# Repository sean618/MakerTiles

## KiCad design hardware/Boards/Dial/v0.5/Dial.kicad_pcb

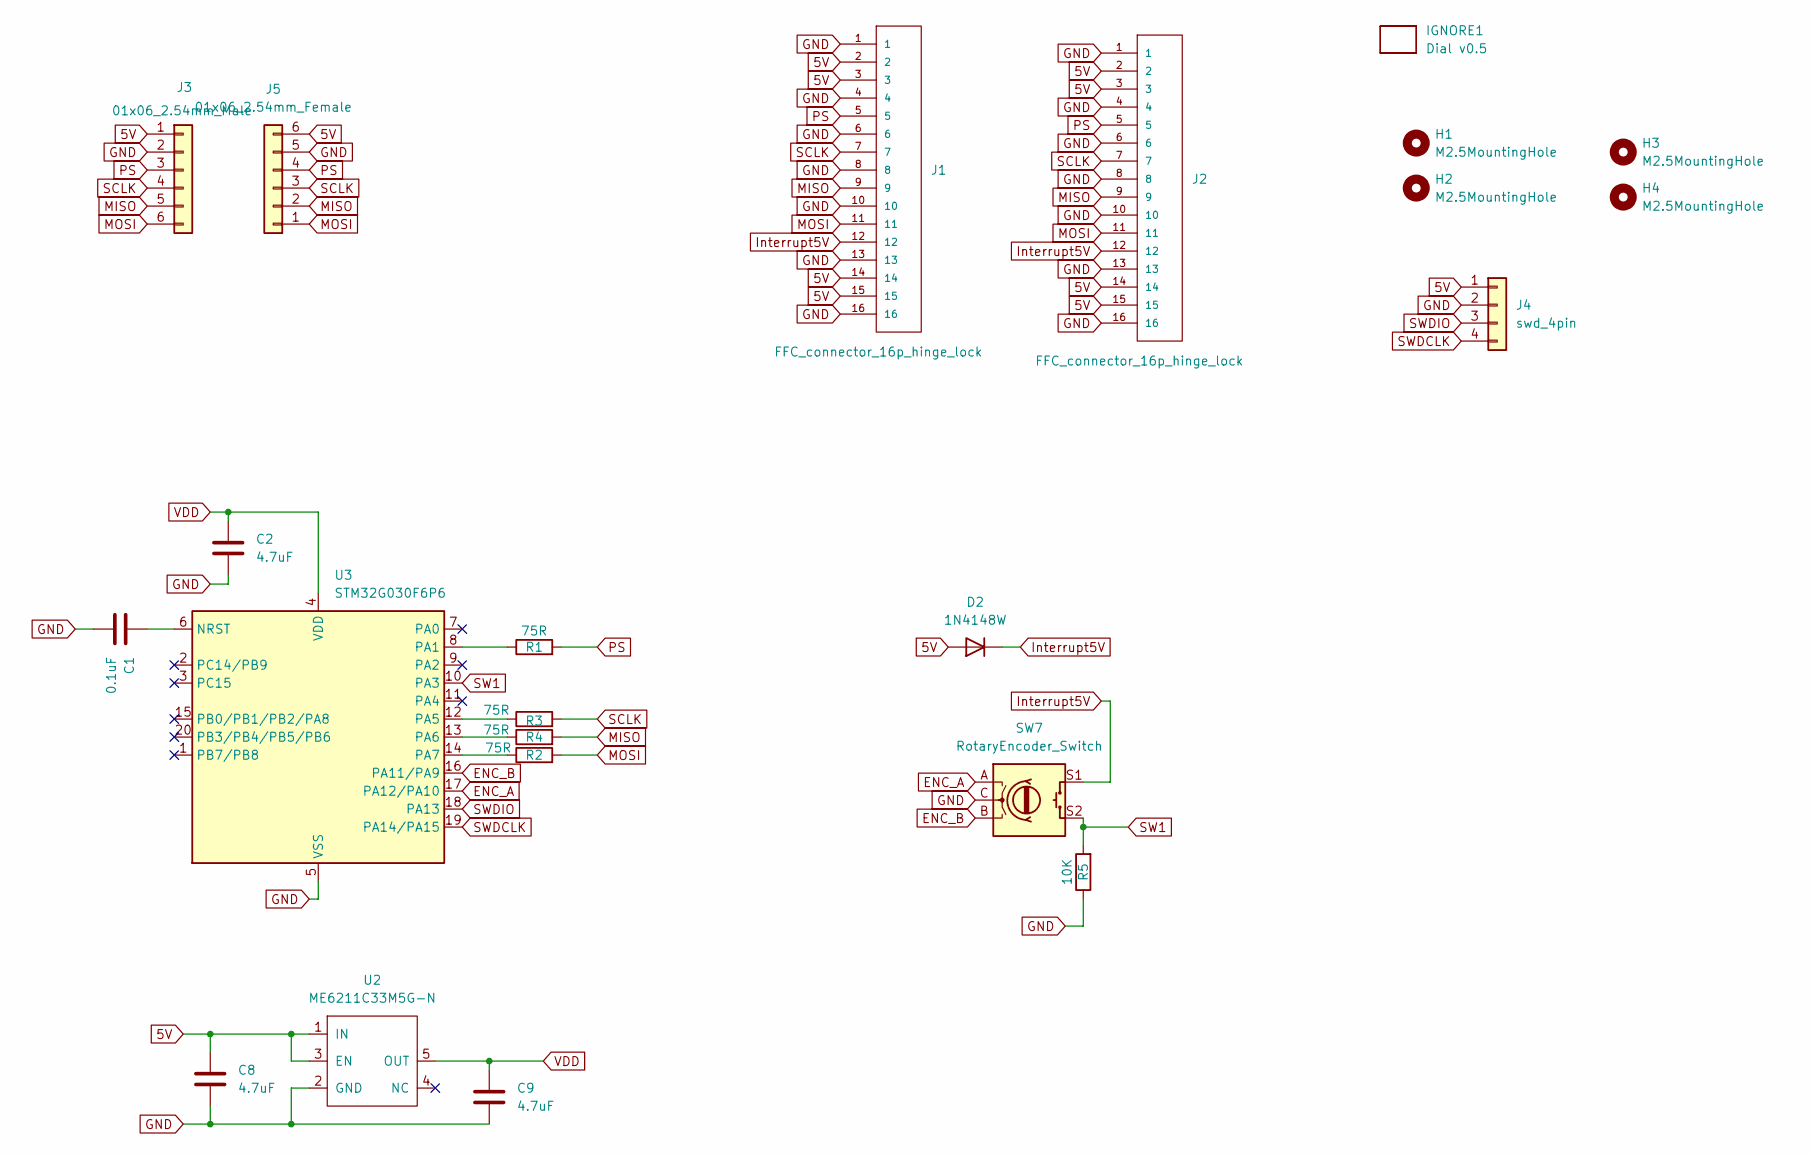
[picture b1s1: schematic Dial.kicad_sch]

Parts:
C1: 0.1uF; C_0402_1005Metric
C2, C8, C9: 4.7uF; C_0402_1005Metric
D2: 1N4148W; D_SOD-123
H1, H2, H3, H4: M2.5MountingHole; MountingHole_2.7mm_M2.5_ISO7380
IGNORE1: Dial v0.5; BoardText
J1, J2: FFC_connector_16p_hinge_lock
J3: 01x06_2.54mm_Male
J4: swd_4pin; swd_header
J5: 01x06_2.54mm_Female
R1, R2, R3, R4: 75R; R_0402_1005Metric
R5: 10K; R_0402_1005Metric
SW7: RotaryEncoder_Switch; RotaryEncoderEC12D
U2: ME6211C33M5G-N; SOT-23-5
U3: STM32G030F6P6; TSSOP-20_4.4x6.5mm_P0.65mm

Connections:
5V: C8.1, D2.2 (A), J1.2, J1.3, J1.14, J1.15, J2.2, J2.3, J2.14, J2.15, J3.1, J4.1, J5.6, U2.1 (IN), U2.3 (EN)
ENC_A: SW7.A, U3.17 (PA12/PA10)
ENC_B: SW7.B, U3.16 (PA11/PA9)
GND: C1.2, C2.2, C8.2, C9.2, J1.1, J1.4, J1.6, J1.8, J1.10, J1.13, J1.16, J2.1, J2.4, J2.6, J2.8, J2.10, J2.13, J2.16, J3.2, J4.2, J5.5, R5.1, SW7.C, U2.2 (GND), U3.5 (VSS)
Interrupt5V: D2.1 (K), J1.12, J2.12, SW7.S1
MISO: J1.9, J2.9, J3.5, J5.2, R4.2
MOSI: J1.11, J2.11, J3.6, J5.1, R2.2
unnamed: C1.1, U3.6 (NRST)
unnamed: R1.1, U3.8 (PA1)
unnamed: R3.1, U3.12 (PA5)
unnamed: R4.1, U3.13 (PA6)
unnamed: R2.1, U3.14 (PA7)
PS: J1.5, J2.5, J3.3, J5.4, R1.2
SCLK: J1.7, J2.7, J3.4, J5.3, R3.2
SW1: R5.2, SW7.S2, U3.10 (PA3)
SWDCLK: J4.4, U3.19 (PA14/PA15)
SWDIO: J4.3, U3.18 (PA13)
VDD: C2.1, C9.1, U2.5 (OUT), U3.4 (VDD)

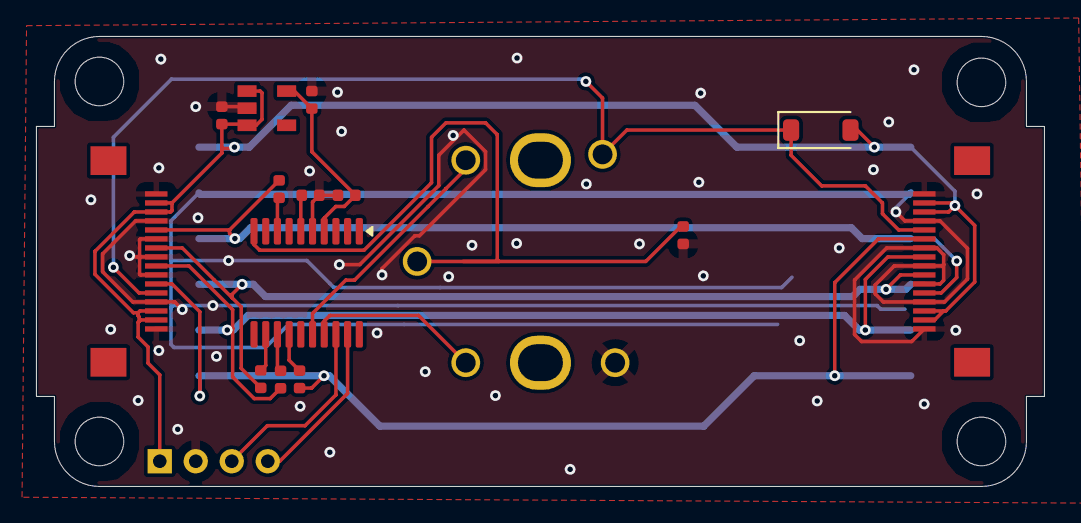
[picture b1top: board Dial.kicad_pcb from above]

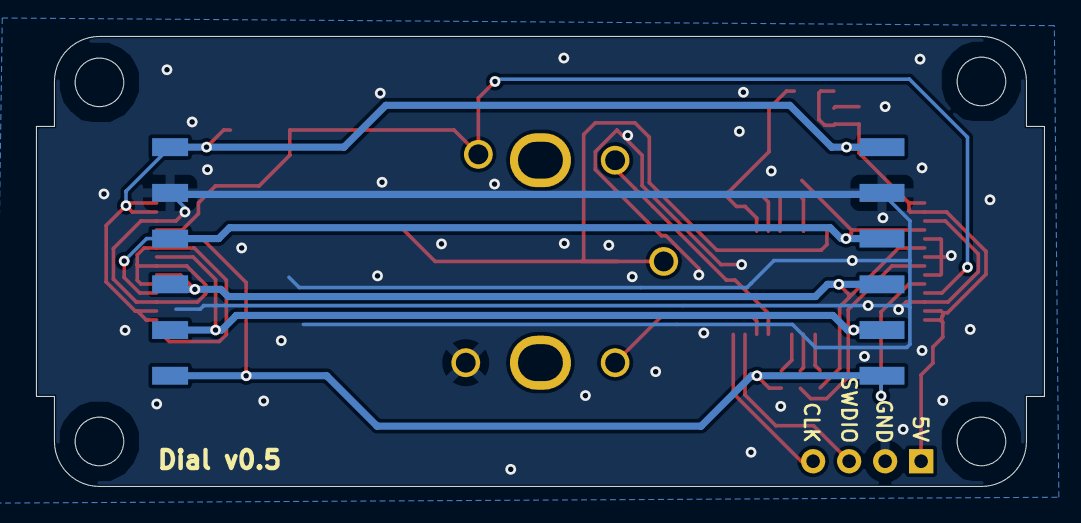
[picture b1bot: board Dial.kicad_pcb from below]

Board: 2 copper layers, 56.0 x 25.0 mm, 23 parts (2 on the bottom side), 18 nets.

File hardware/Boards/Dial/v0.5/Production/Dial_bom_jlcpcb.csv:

Comment,Designator,Footprint,LCSC Part Number
4.7uF,"C9,C8,C2",C_0402_1005Metric,C23733
FFC_connector_16p_hinge_lock,"J1,J2",FFC_connector_16p_hinge_lock,C262665
1N4148W,D2,D_SOD-123,C81598
ME6211C33M5G-N,U2,SOT-23-5,C81233
75R,"R2,R4,R1,R3",R_0402_1005Metric,C25133
RotaryEncoder_Switch,SW7,RotaryEncoderEC12D,C112349
STM32G030F6P6,U3,TSSOP-20_4.4x6.5mm_P0.65mm,C529330
10K,R5,R_0402_1005Metric,C25744
0.1uF,C1,C_0402_1005Metric,C1525
01x06_2.54mm_Female,J5,01x06_2.54mm_Female,C5142239
01x06_2.54mm_Male,J3,01x06_2.54mm_Male,C5242199

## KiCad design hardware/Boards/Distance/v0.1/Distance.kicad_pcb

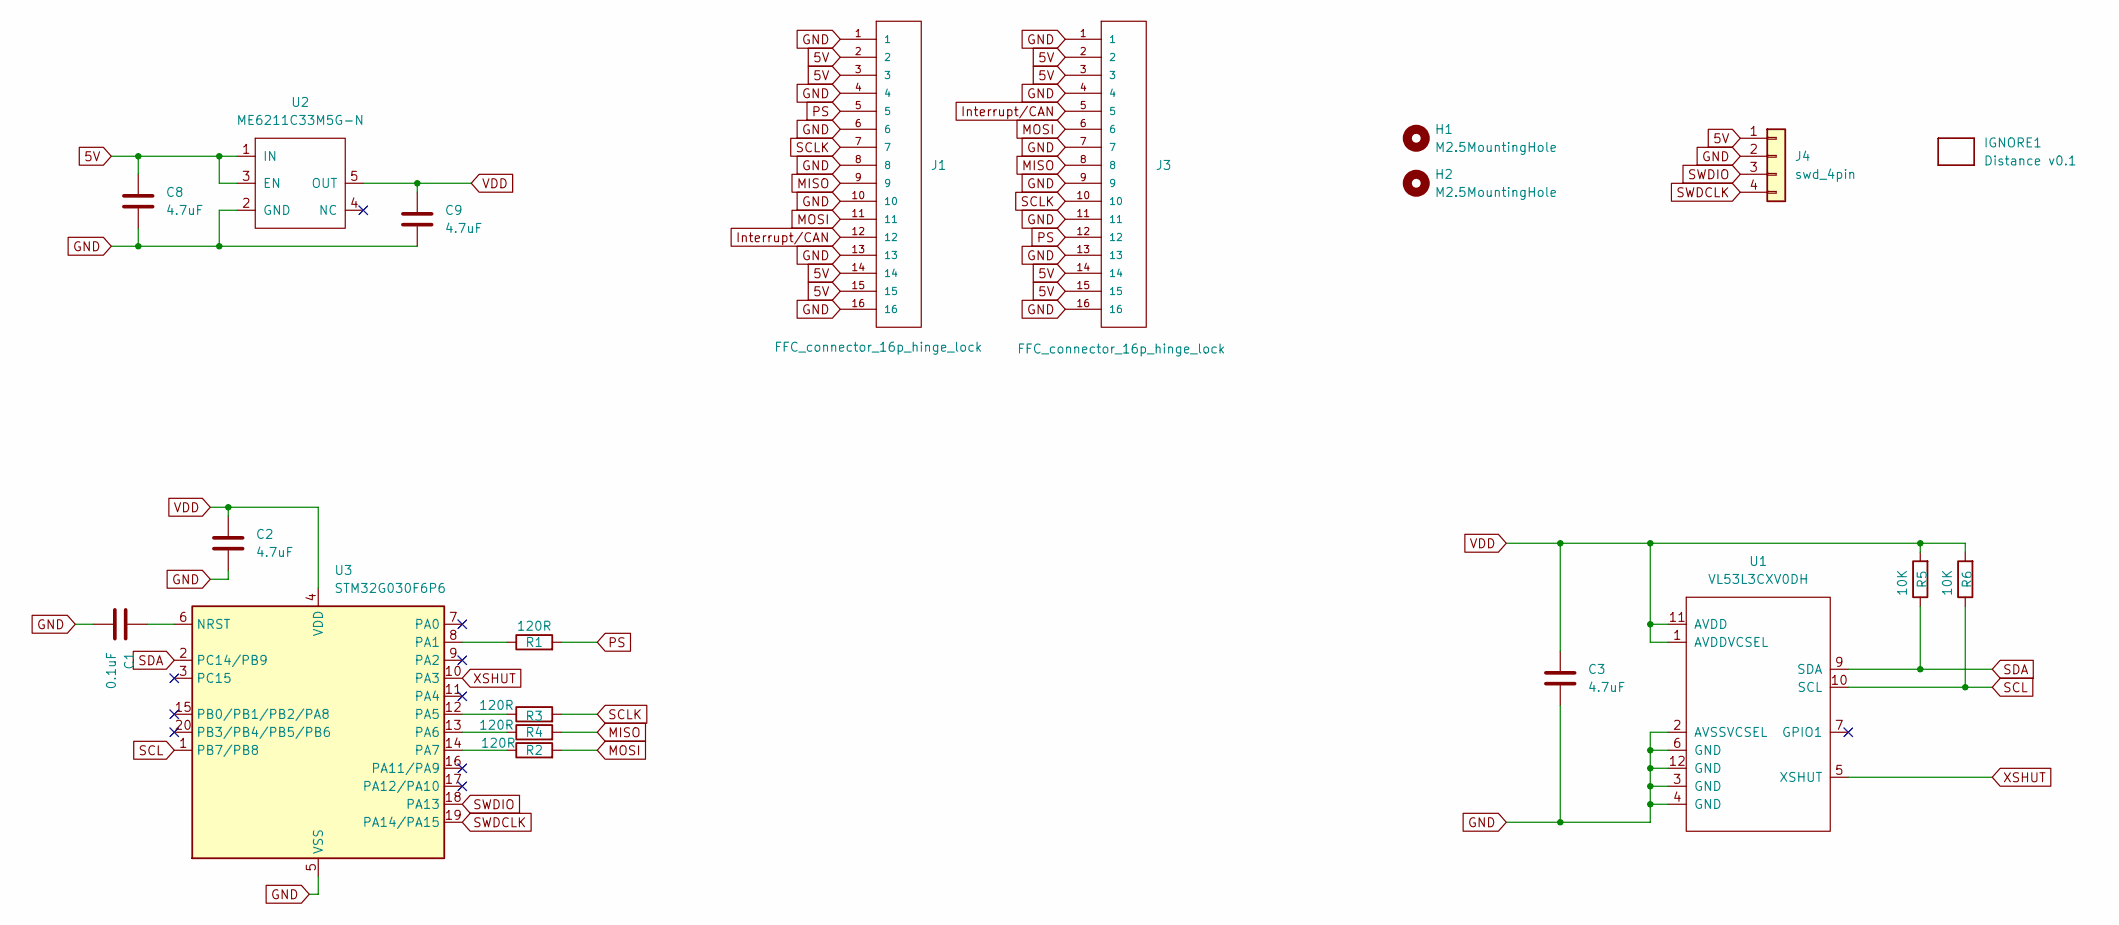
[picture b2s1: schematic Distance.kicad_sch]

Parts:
C1: 0.1uF; C_0402_1005Metric
C2, C3, C8, C9: 4.7uF; C_0402_1005Metric
H1, H2: M2.5MountingHole; MountingHole_2.7mm_M2.5_ISO7380
IGNORE1: Distance v0.1; BoardText
J1, J3: FFC_connector_16p_hinge_lock
J4: swd_4pin; swd_header
R1, R2, R3, R4: 120R; R_0402_1005Metric
R5, R6: 10K; R_0402_1005Metric
U1: VL53L3CXV0DH
U2: ME6211C33M5G-N; SOT-23-5
U3: STM32G030F6P6; TSSOP-20_4.4x6.5mm_P0.65mm

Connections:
5V: C8.1, J1.2, J1.3, J1.14, J1.15, J3.2, J3.3, J3.14, J3.15, J4.1, U2.1 (IN), U2.3 (EN)
GND: C1.2, C2.2, C3.2, C8.2, C9.2, J1.1, J1.4, J1.6, J1.8, J1.10, J1.13, J1.16, J3.1, J3.4, J3.7, J3.9, J3.11, J3.13, J3.16, J4.2, U1.2 (AVSSVCSEL), U1.3 (GND), U1.4 (GND), U1.6 (GND), U1.12 (GND), U2.2 (GND), U3.5 (VSS)
Interrupt/CAN: J1.12, J3.5
MISO: J1.9, J3.8, R4.2
MOSI: J1.11, J3.6, R2.2
unnamed: C1.1, U3.6 (NRST)
unnamed: R1.1, U3.8 (PA1)
unnamed: R3.1, U3.12 (PA5)
unnamed: R4.1, U3.13 (PA6)
unnamed: R2.1, U3.14 (PA7)
PS: J1.5, J3.12, R1.2
SCL: R6.1, U1.10 (SCL), U3.1 (PB7/PB8)
SCLK: J1.7, J3.10, R3.2
SDA: R5.1, U1.9 (SDA), U3.2 (PC14/PB9)
SWDCLK: J4.4, U3.19 (PA14/PA15)
SWDIO: J4.3, U3.18 (PA13)
VDD: C2.1, C3.1, C9.1, R5.2, R6.2, U1.1 (AVDDVCSEL), U1.11 (AVDD), U2.5 (OUT), U3.4 (VDD)
XSHUT: U1.5 (XSHUT), U3.10 (PA3)

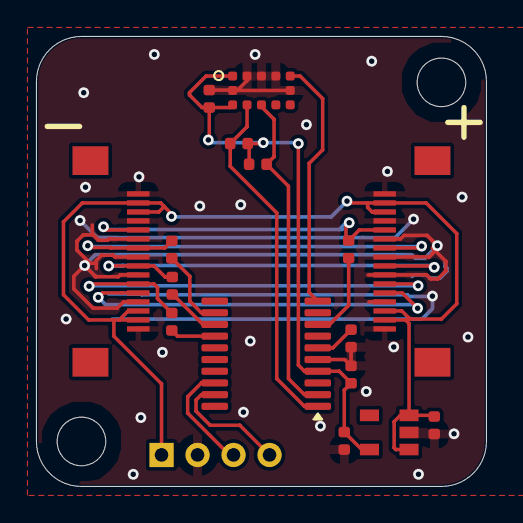
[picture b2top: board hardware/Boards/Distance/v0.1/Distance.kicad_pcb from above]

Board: 4 copper layers, 25.0 x 25.0 mm, 20 parts (0 on the bottom side), 18 nets.

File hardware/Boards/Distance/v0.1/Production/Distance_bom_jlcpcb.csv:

Comment,Designator,Footprint,LCSC Part Number
4.7uF,"C9,C8,C2,C3",C_0402_1005Metric,C23733
FFC_connector_16p_hinge_lock,"J1,J3",FFC_connector_16p_hinge_lock,C262665
10K,"R5,R6",R_0402_1005Metric,C25744
ME6211C33M5G-N,U2,SOT-23-5,C81233
VL53L3CXV0DH,U1,VL53L3CXV0DH,C1864163
120R,"R2,R3,R4,R1",R_0402_1005Metric,C25079
STM32G030F6P6,U3,TSSOP-20_4.4x6.5mm_P0.65mm,C529330
0.1uF,C1,C_0402_1005Metric,C1525

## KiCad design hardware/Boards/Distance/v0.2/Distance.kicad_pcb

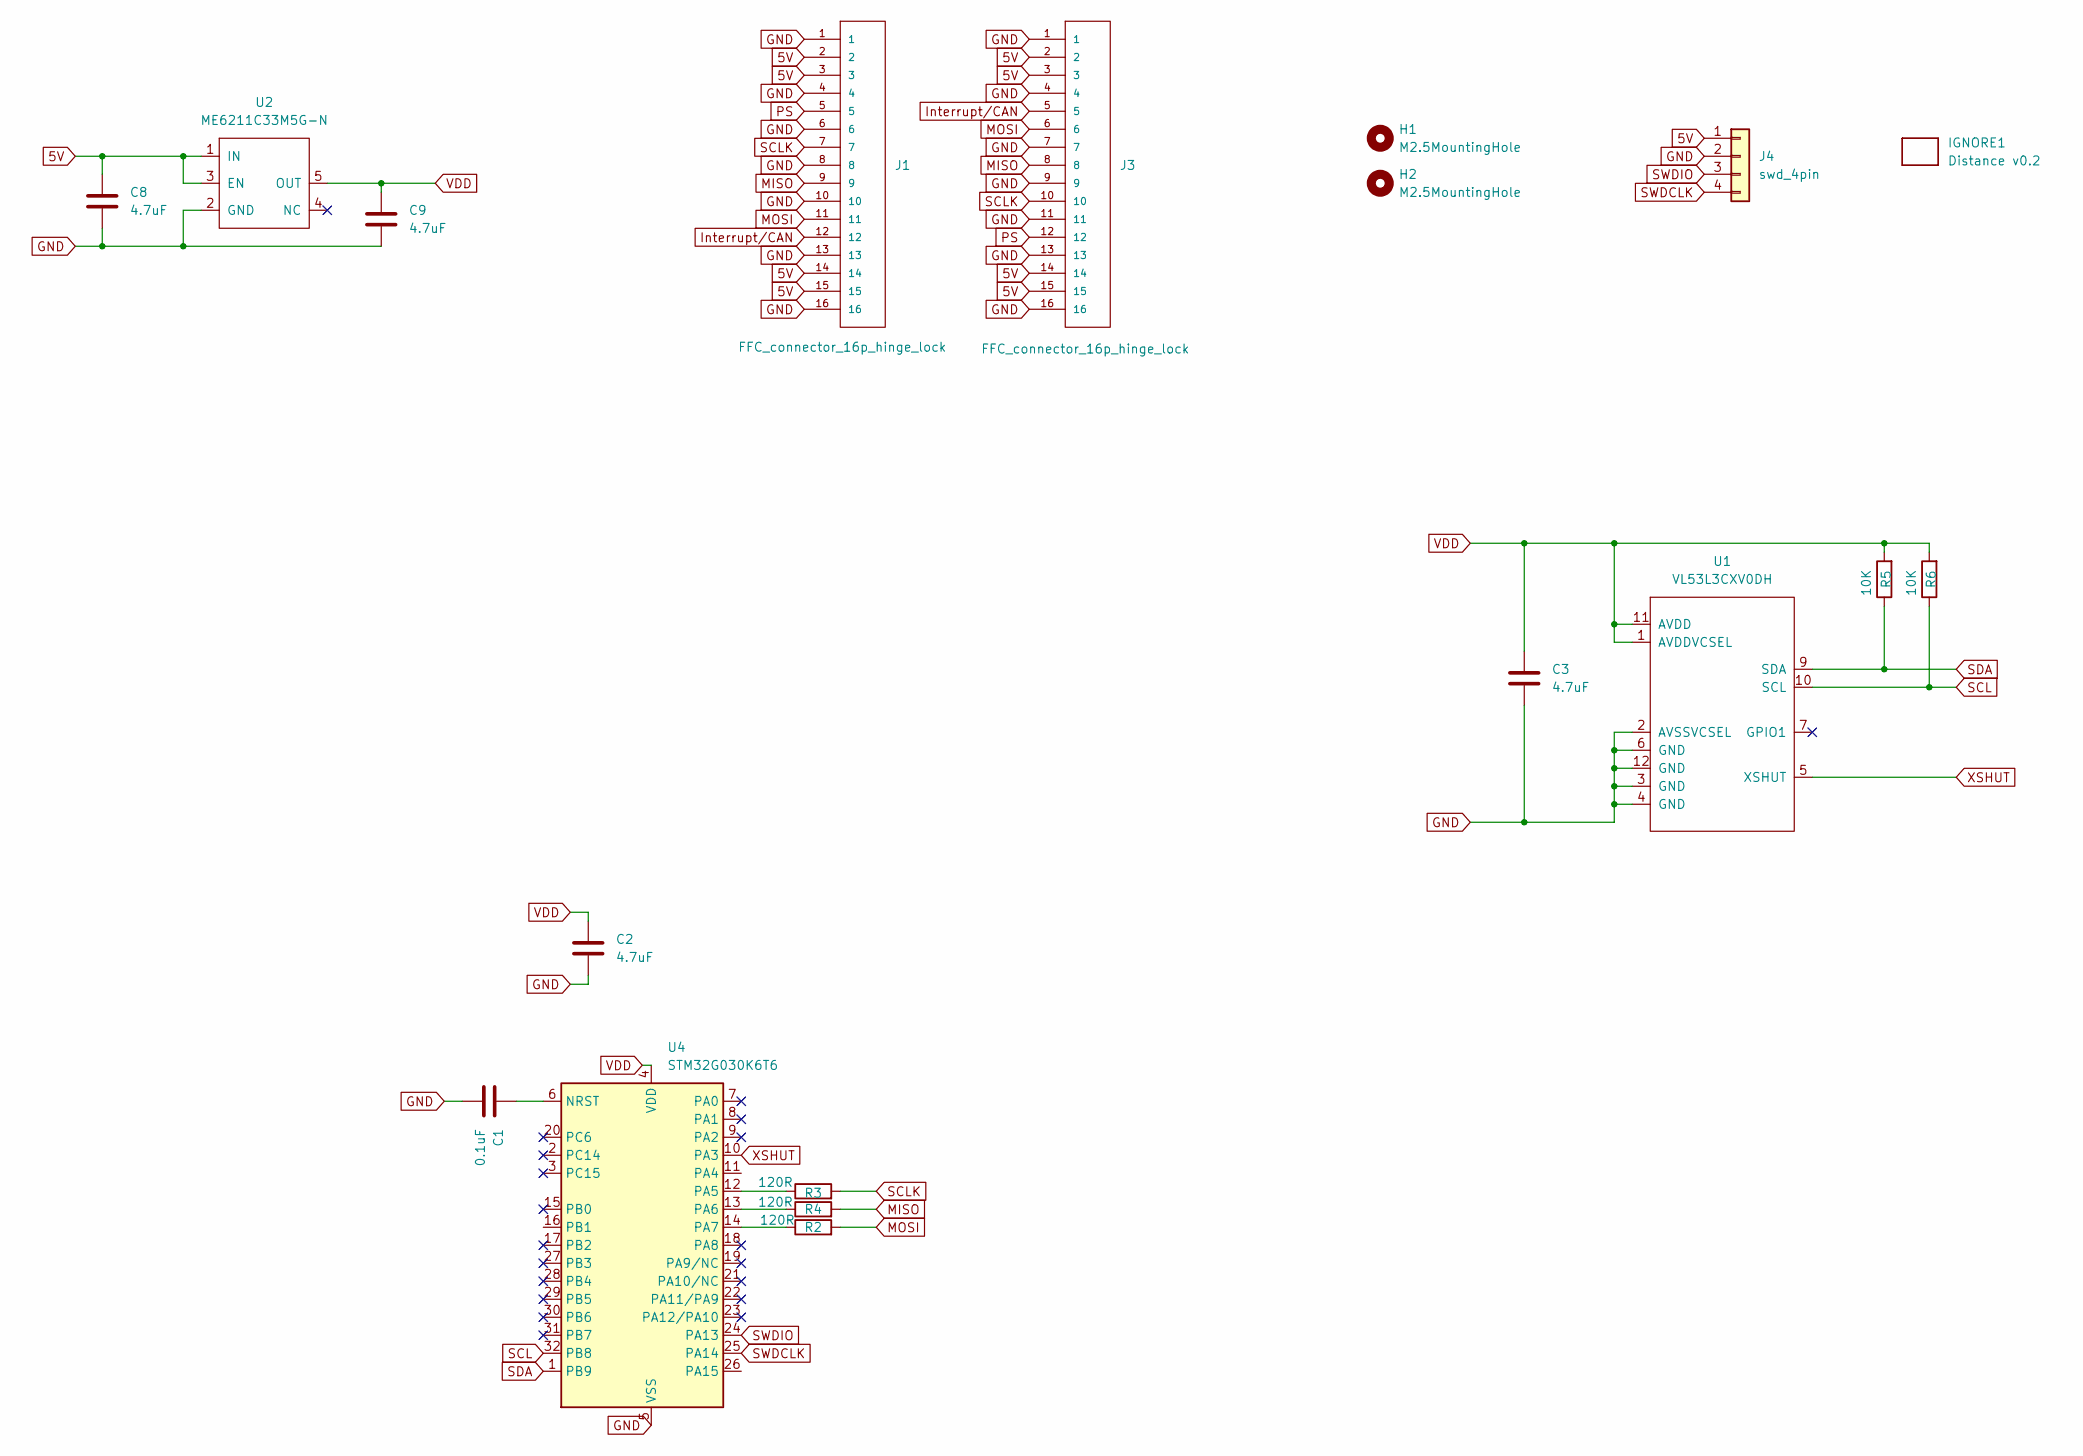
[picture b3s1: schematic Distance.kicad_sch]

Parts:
C1: 0.1uF; C_0402_1005Metric
C2, C3, C8, C9: 4.7uF; C_0402_1005Metric
H1, H2: M2.5MountingHole; MountingHole_2.7mm_M2.5_ISO7380
IGNORE1: Distance v0.2; BoardText
J1, J3: FFC_connector_16p_hinge_lock
J4: swd_4pin; swd_header
R2, R3, R4: 120R; R_0402_1005Metric
R5, R6: 10K; R_0402_1005Metric
U1: VL53L3CXV0DH
U2: ME6211C33M5G-N; SOT-23-5
U4: STM32G030K6T6; LQFP-32_7x7mm_P0.8mm

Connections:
5V: C8.1, J1.2, J1.3, J1.14, J1.15, J3.2, J3.3, J3.14, J3.15, J4.1, U2.1 (IN), U2.3 (EN)
GND: C1.2, C2.2, C3.2, C8.2, C9.2, J1.1, J1.4, J1.6, J1.8, J1.10, J1.13, J1.16, J3.1, J3.4, J3.7, J3.9, J3.11, J3.13, J3.16, J4.2, U1.2 (AVSSVCSEL), U1.3 (GND), U1.4 (GND), U1.6 (GND), U1.12 (GND), U2.2 (GND), U4.5 (VSS)
Interrupt/CAN: J1.12, J3.5
MISO: J1.9, J3.8, R4.2
MOSI: J1.11, J3.6, R2.2
unnamed: C1.1, U4.6 (NRST)
unnamed: R3.1, U4.12 (PA5)
unnamed: R4.1, U4.13 (PA6)
unnamed: R2.1, U4.14 (PA7)
PS: J1.5, J3.12
SCL: R6.1, U1.10 (SCL), U4.32 (PB8)
SCLK: J1.7, J3.10, R3.2
SDA: R5.1, U1.9 (SDA), U4.1 (PB9)
SWDCLK: J4.4, U4.25 (PA14)
SWDIO: J4.3, U4.24 (PA13)
VDD: C2.1, C3.1, C9.1, R5.2, R6.2, U1.1 (AVDDVCSEL), U1.11 (AVDD), U2.5 (OUT), U4.4 (VDD)
XSHUT: U1.5 (XSHUT), U4.10 (PA3)

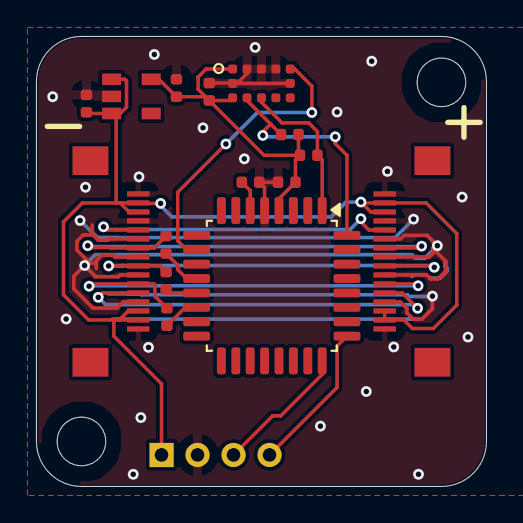
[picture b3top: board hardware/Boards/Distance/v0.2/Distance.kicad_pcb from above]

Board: 4 copper layers, 25.0 x 25.0 mm, 19 parts (0 on the bottom side), 17 nets.

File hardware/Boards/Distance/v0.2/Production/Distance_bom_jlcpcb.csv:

Comment,Designator,Footprint,LCSC Part Number
4.7uF,"C9,C8,C2,C3",C_0402_1005Metric,C23733
FFC_connector_16p_hinge_lock,"J1,J3",FFC_connector_16p_hinge_lock,C262665
10K,"R5,R6",R_0402_1005Metric,C25744
ME6211C33M5G-N,U2,SOT-23-5,C81233
VL53L3CXV0DH,U1,VL53L3CXV0DH,C1864163
120R,"R2,R3,R4",R_0402_1005Metric,C25079
0.1uF,C1,C_0402_1005Metric,C1525
STM32G030K6T6,U4,LQFP-32_7x7mm_P0.8mm,C529331

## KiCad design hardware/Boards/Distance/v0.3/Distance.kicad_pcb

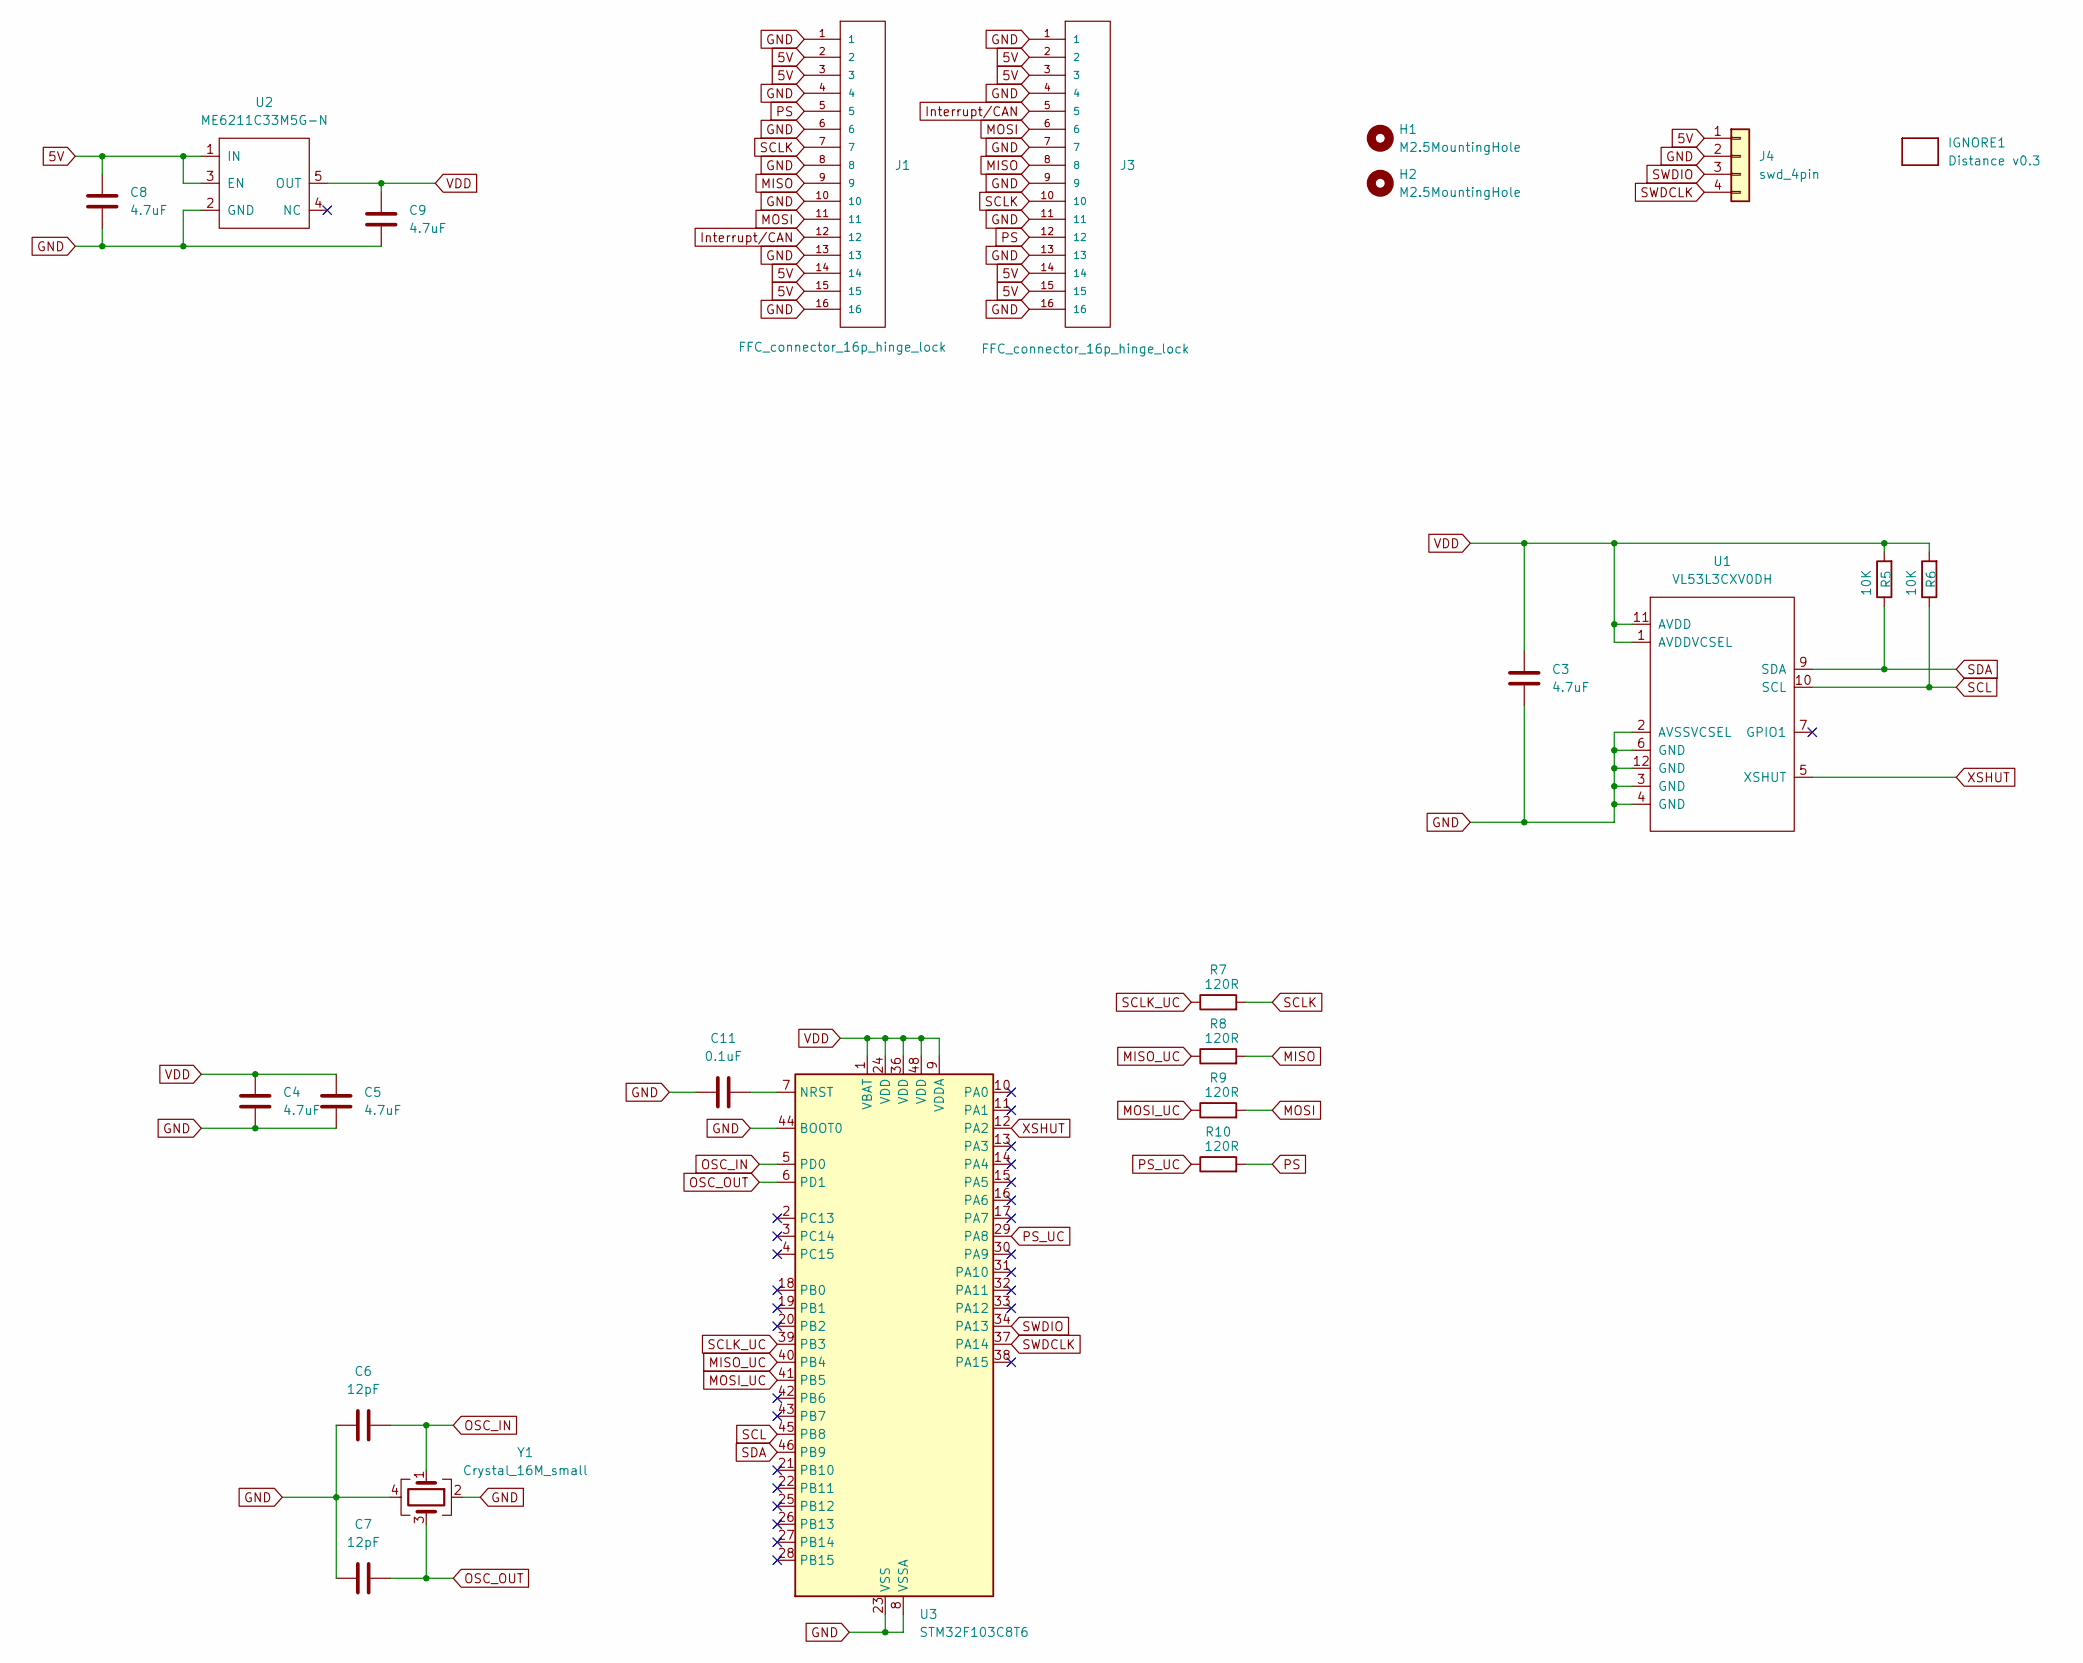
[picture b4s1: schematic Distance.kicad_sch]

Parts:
C3, C4, C5, C8, C9: 4.7uF; C_0402_1005Metric
C6, C7: 12pF; C_0402_1005Metric
C11: 0.1uF; C_0402_1005Metric
H1, H2: M2.5MountingHole; MountingHole_2.7mm_M2.5_ISO7380
IGNORE1: Distance v0.3; BoardText
J1, J3: FFC_connector_16p_hinge_lock
J4: swd_4pin; swd_header
R5, R6: 10K; R_0402_1005Metric
R7, R8, R9, R10: 120R; R_0402_1005Metric
U1: VL53L3CXV0DH
U2: ME6211C33M5G-N; SOT-23-5
U3: STM32F103C8T6; LQFP-48_7x7mm_P0.5mm
Y1: Crystal_16M_small; Crystal_SMD_2016-4Pin_2.0x1.6mm

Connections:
5V: C8.1, J1.2, J1.3, J1.14, J1.15, J3.2, J3.3, J3.14, J3.15, J4.1, U2.1 (IN), U2.3 (EN)
GND: C3.2, C4.2, C5.2, C6.1, C7.1, C8.2, C9.2, C11.1, J1.1, J1.4, J1.6, J1.8, J1.10, J1.13, J1.16, J3.1, J3.4, J3.7, J3.9, J3.11, J3.13, J3.16, J4.2, U1.2 (AVSSVCSEL), U1.3 (GND), U1.4 (GND), U1.6 (GND), U1.12 (GND), U2.2 (GND), U3.8 (VSSA), U3.23 (VSS), U3.35 (VSS), U3.44 (BOOT0), U3.47 (VSS), Y1.2 (GND), Y1.4 (GND)
Interrupt/CAN: J1.12, J3.5
MISO: J1.9, J3.8, R8.2
MISO_UC: R8.1, U3.40 (PB4)
MOSI: J1.11, J3.6, R9.2
MOSI_UC: R9.1, U3.41 (PB5)
unnamed: C11.2, U3.7 (NRST)
OSC_IN: C6.2, U3.5 (PD0), Y1.1
OSC_OUT: C7.2, U3.6 (PD1), Y1.3
PS: J1.5, J3.12, R10.2
PS_UC: R10.1, U3.29 (PA8)
SCL: R6.1, U1.10 (SCL), U3.45 (PB8)
SCLK: J1.7, J3.10, R7.2
SCLK_UC: R7.1, U3.39 (PB3)
SDA: R5.1, U1.9 (SDA), U3.46 (PB9)
SWDCLK: J4.4, U3.37 (PA14)
SWDIO: J4.3, U3.34 (PA13)
VDD: C3.1, C4.1, C5.1, C9.1, R5.2, R6.2, U1.1 (AVDDVCSEL), U1.11 (AVDD), U2.5 (OUT), U3.1 (VBAT), U3.9 (VDDA), U3.24 (VDD), U3.36 (VDD), U3.48 (VDD)
XSHUT: U1.5 (XSHUT), U3.12 (PA2)

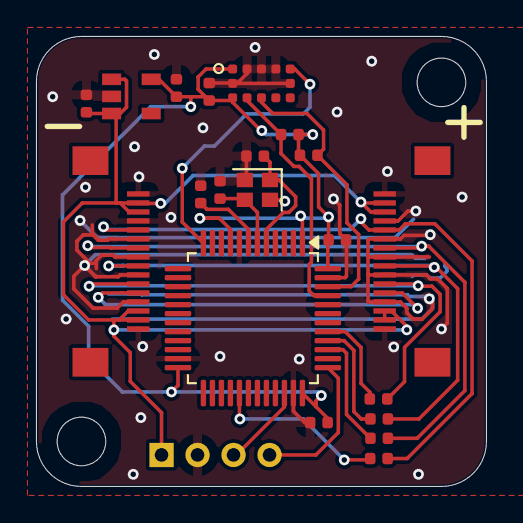
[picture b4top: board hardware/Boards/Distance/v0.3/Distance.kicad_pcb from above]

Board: 4 copper layers, 25.0 x 25.0 mm, 24 parts (0 on the bottom side), 20 nets.

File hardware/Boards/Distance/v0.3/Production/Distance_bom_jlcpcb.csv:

Comment,Designator,Footprint,LCSC Part Number
4.7uF,"C9,C8,C5,C3,C4",C_0402_1005Metric,C23733
FFC_connector_16p_hinge_lock,"J1,J3",FFC_connector_16p_hinge_lock,C262665
12pF,"C6,C7",C_0402_1005Metric,C1547
120R,"R8,R10,R9,R7",R_0402_1005Metric,C25079
0.1uF,C11,C_0402_1005Metric,C1525
10K,"R5,R6",R_0402_1005Metric,C25744
STM32F103C8T6,U3,LQFP-48_7x7mm_P0.5mm,C2969777
ME6211C33M5G-N,U2,SOT-23-5,C81233
VL53L3CXV0DH,U1,VL53L3CXV0DH,C1864163
Crystal_16M_small,Y1,Crystal_SMD_2016-4Pin_2.0x1.6mm,C252270

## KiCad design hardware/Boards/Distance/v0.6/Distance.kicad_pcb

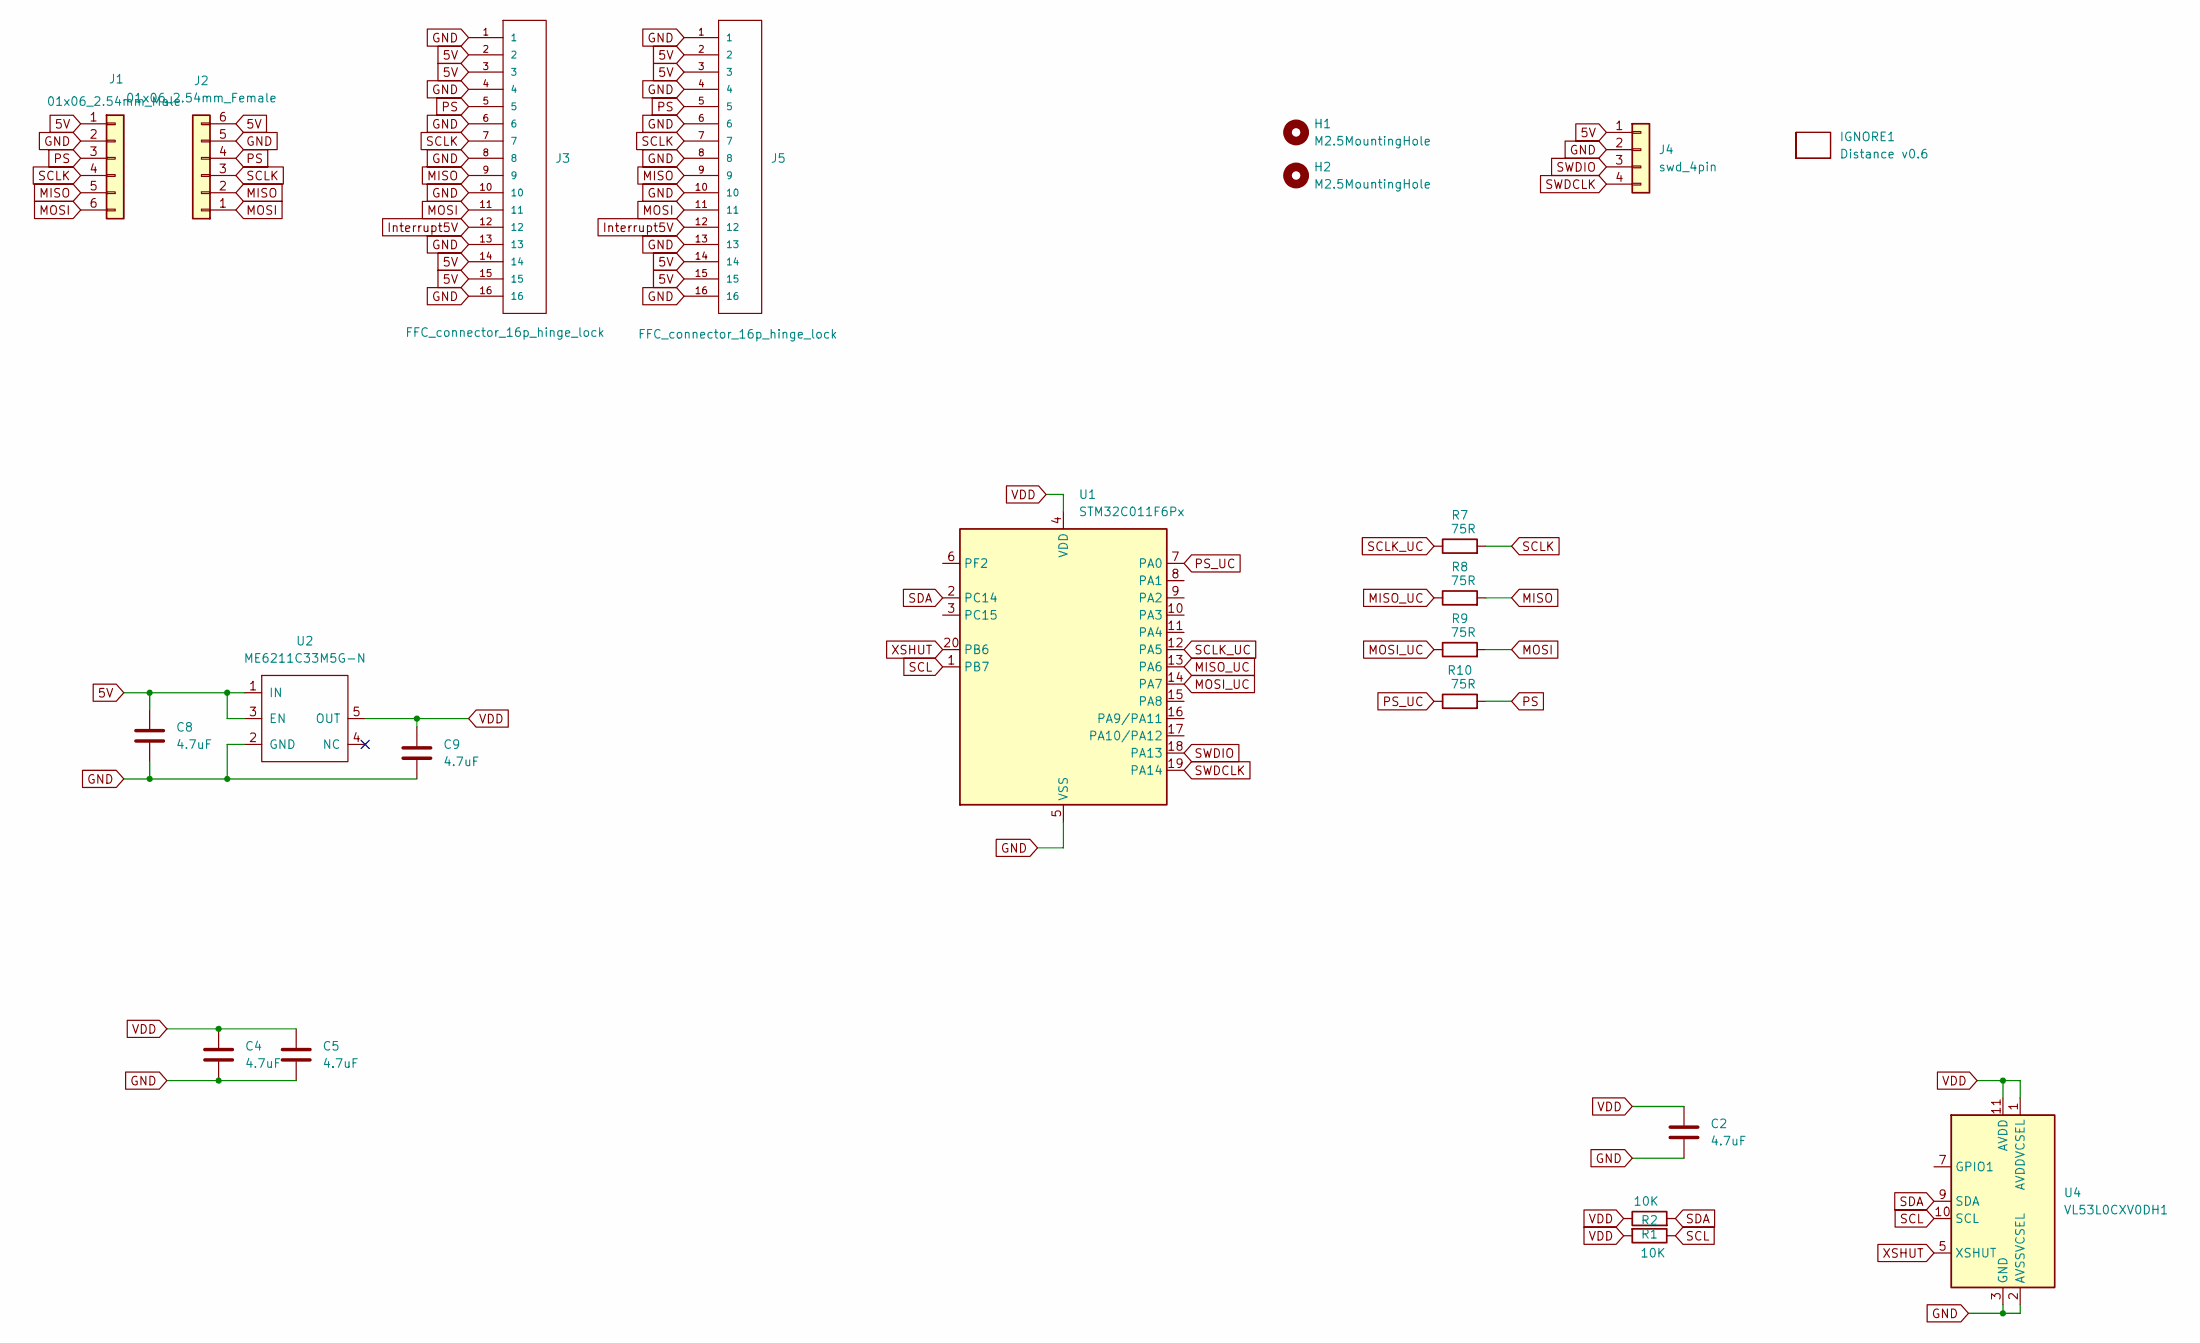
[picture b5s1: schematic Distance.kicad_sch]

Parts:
C2, C4, C5, C8, C9: 4.7uF; C_0402_1005Metric
H1, H2: M2.5MountingHole; MountingHole_2.7mm_M2.5_ISO7380
IGNORE1: Distance v0.6; BoardText
J1: 01x06_2.54mm_Male
J2: 01x06_2.54mm_Female
J3, J5: FFC_connector_16p_hinge_lock
J4: swd_4pin; swd_header
R1, R2: 10K; R_0402_1005Metric
R7, R8, R9, R10: 75R; R_0402_1005Metric
U1: STM32C011F6Px; TSSOP-20_4.4x6.5mm_P0.65mm
U2: ME6211C33M5G-N; SOT-23-5
U4: VL53L0CXV0DH1; ST_VL53L1x

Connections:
5V: C8.1, J1.1, J2.6, J3.2, J3.3, J3.14, J3.15, J4.1, J5.2, J5.3, J5.14, J5.15, U2.1 (IN), U2.3 (EN)
GND: C2.2, C4.2, C5.2, C8.2, C9.2, J1.2, J2.5, J3.1, J3.4, J3.6, J3.8, J3.10, J3.13, J3.16, J4.2, J5.1, J5.4, J5.6, J5.8, J5.10, J5.13, J5.16, U1.5 (VSS), U2.2 (GND), U4.2 (AVSSVCSEL), U4.3 (GND), U4.4 (GND), U4.6 (GND), U4.12 (GND)
Interrupt5V: J3.12, J5.12
MISO: J1.5, J2.2, J3.9, J5.9, R8.2
MISO_UC: R8.1, U1.13 (PA6)
MOSI: J1.6, J2.1, J3.11, J5.11, R9.2
MOSI_UC: R9.1, U1.14 (PA7)
PS: J1.3, J2.4, J3.5, J5.5, R10.2
PS_UC: R10.1, U1.7 (PA0)
SCL: R1.1, U1.1 (PB7), U4.10 (SCL)
SCLK: J1.4, J2.3, J3.7, J5.7, R7.2
SCLK_UC: R7.1, U1.12 (PA5)
SDA: R2.2, U1.2 (PC14), U4.9 (SDA)
SWDCLK: J4.4, U1.19 (PA14)
SWDIO: J4.3, U1.18 (PA13)
VDD: C2.1, C4.1, C5.1, C9.1, R1.2, R2.1, U1.4 (VDD), U2.5 (OUT), U4.1 (AVDDVCSEL), U4.11 (AVDD)
XSHUT: U1.20 (PB6), U4.5 (XSHUT)

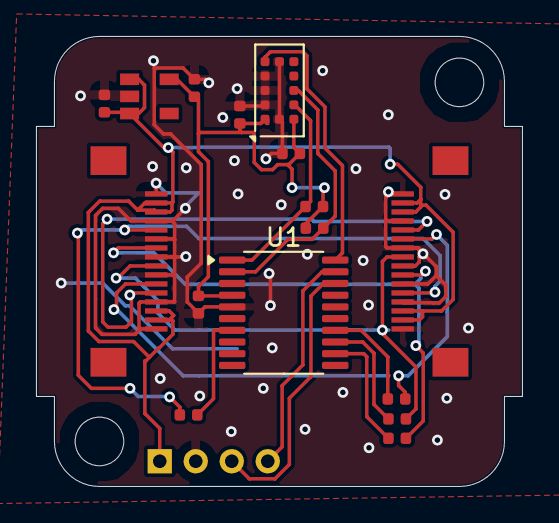
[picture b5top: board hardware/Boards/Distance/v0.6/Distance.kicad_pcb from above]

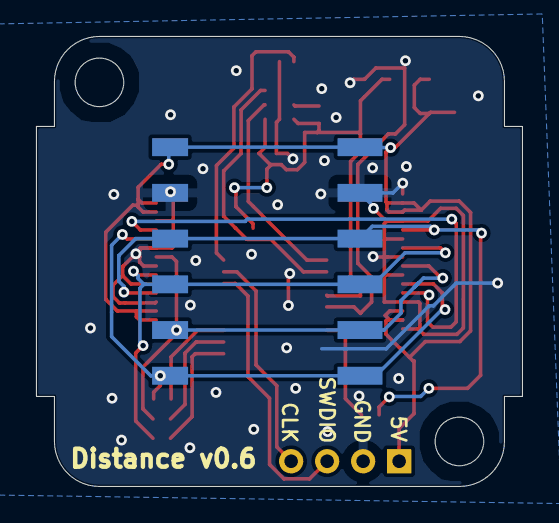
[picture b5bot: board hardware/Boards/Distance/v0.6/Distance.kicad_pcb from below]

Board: 4 copper layers, 27.0 x 25.0 mm, 22 parts (2 on the bottom side), 17 nets.
